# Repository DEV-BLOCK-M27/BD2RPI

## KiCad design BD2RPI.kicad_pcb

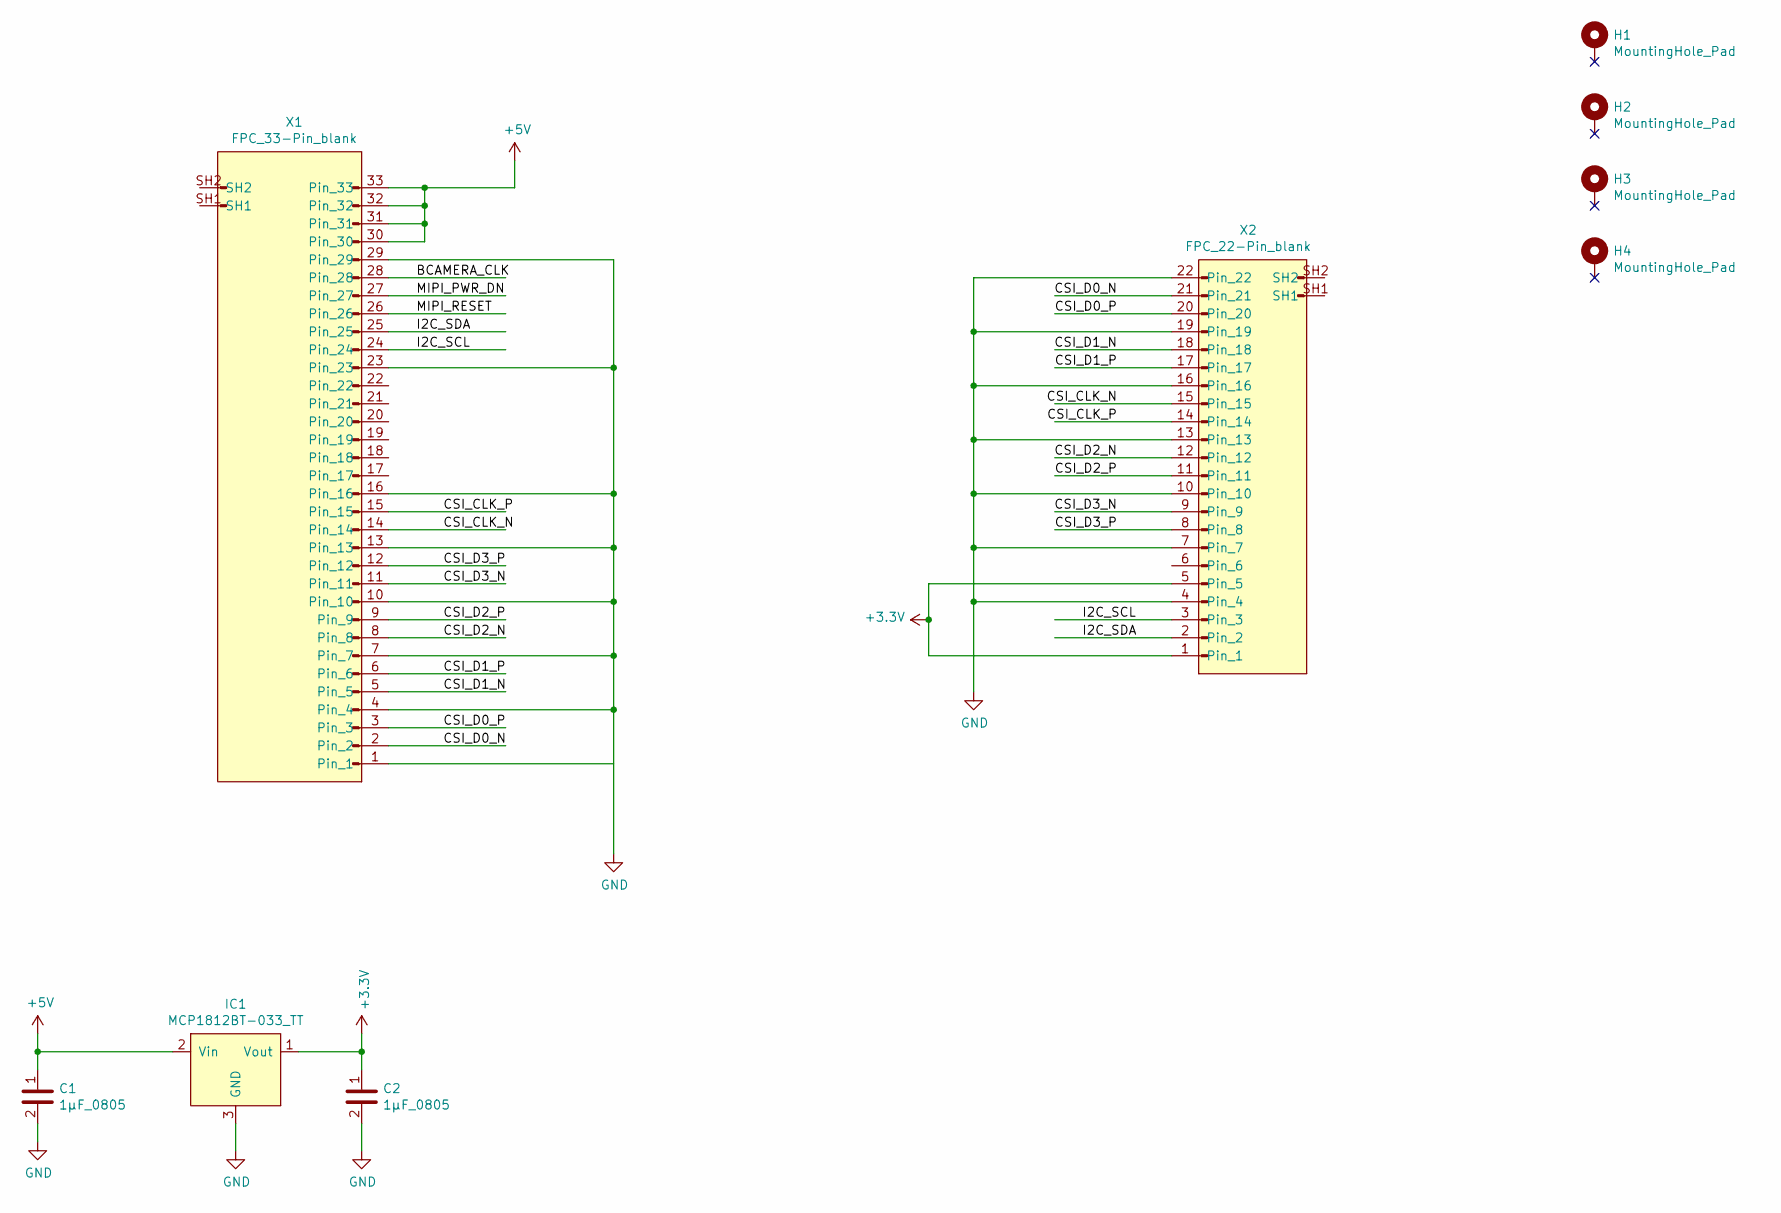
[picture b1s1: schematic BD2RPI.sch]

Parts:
C1, C2: 1µF_0805; C_0805_2012
H1, H2, H3, H4: MountingHole_Pad; MountingHole_3.2mm_M3_DIN965_Pad
IC1: MCP1812BT-033_TT; _SOT-23-123
X1: FPC_33-Pin_blank; OMRON_XF2M-3315-1A
X2: FPC_22-Pin_blank; MOLEX_54548-2271

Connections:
+3V3: C2.1, IC1.1 (Vout), X2.1, X2.5
+5V: C1.1, IC1.2 (Vin), X1.30, X1.31, X1.32, X1.33
/BCAMERA_CLK: X1.28
/CSI_CLK_N: X1.14, X2.15
/CSI_CLK_P: X1.15, X2.14
/CSI_D0_N: X1.2, X2.21
/CSI_D0_P: X1.3, X2.20
/CSI_D1_N: X1.5, X2.18
/CSI_D1_P: X1.6, X2.17
/CSI_D2_N: X1.8, X2.12
/CSI_D2_P: X1.9, X2.11
/CSI_D3_N: X1.11, X2.9
/CSI_D3_P: X1.12, X2.8
/I2C_SCL: X1.24, X2.3
/I2C_SDA: X1.25, X2.2
/MIPI_PWR_DN: X1.27
/MIPI_RESET: X1.26
GND: C1.2, C2.2, IC1.3 (GND), X1.1, X1.4, X1.7, X1.10, X1.13, X1.16, X1.23, X1.29, X2.4, X2.7, X2.10, X2.13, X2.16, X2.19, X2.22

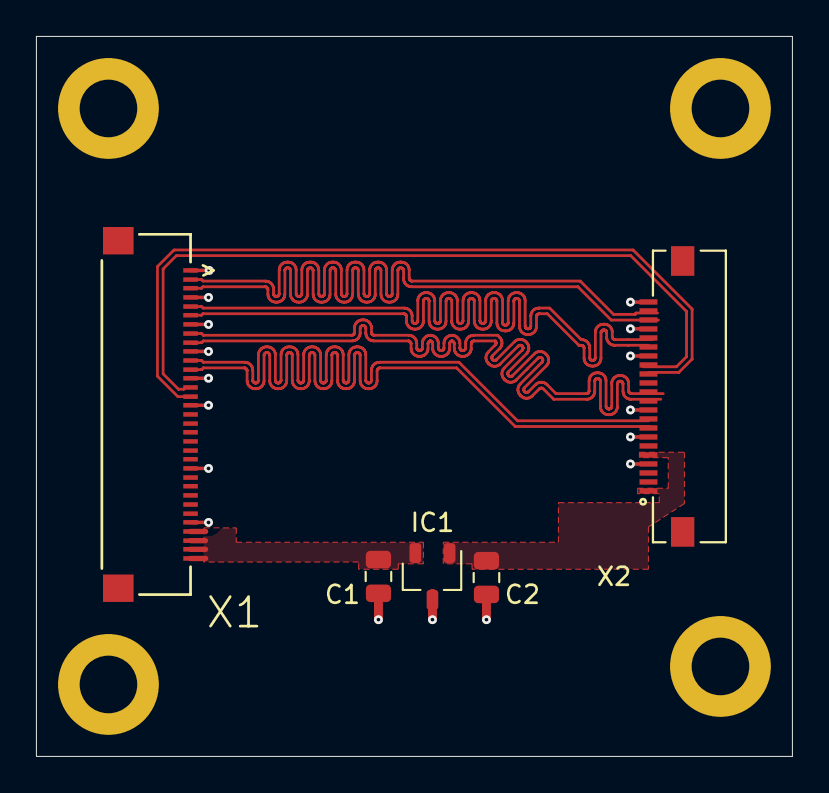
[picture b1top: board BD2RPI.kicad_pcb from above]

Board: 4 copper layers, 42.0 x 40.0 mm, 9 parts (0 on the bottom side), 15 nets.

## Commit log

2021-07-03 inital commit
